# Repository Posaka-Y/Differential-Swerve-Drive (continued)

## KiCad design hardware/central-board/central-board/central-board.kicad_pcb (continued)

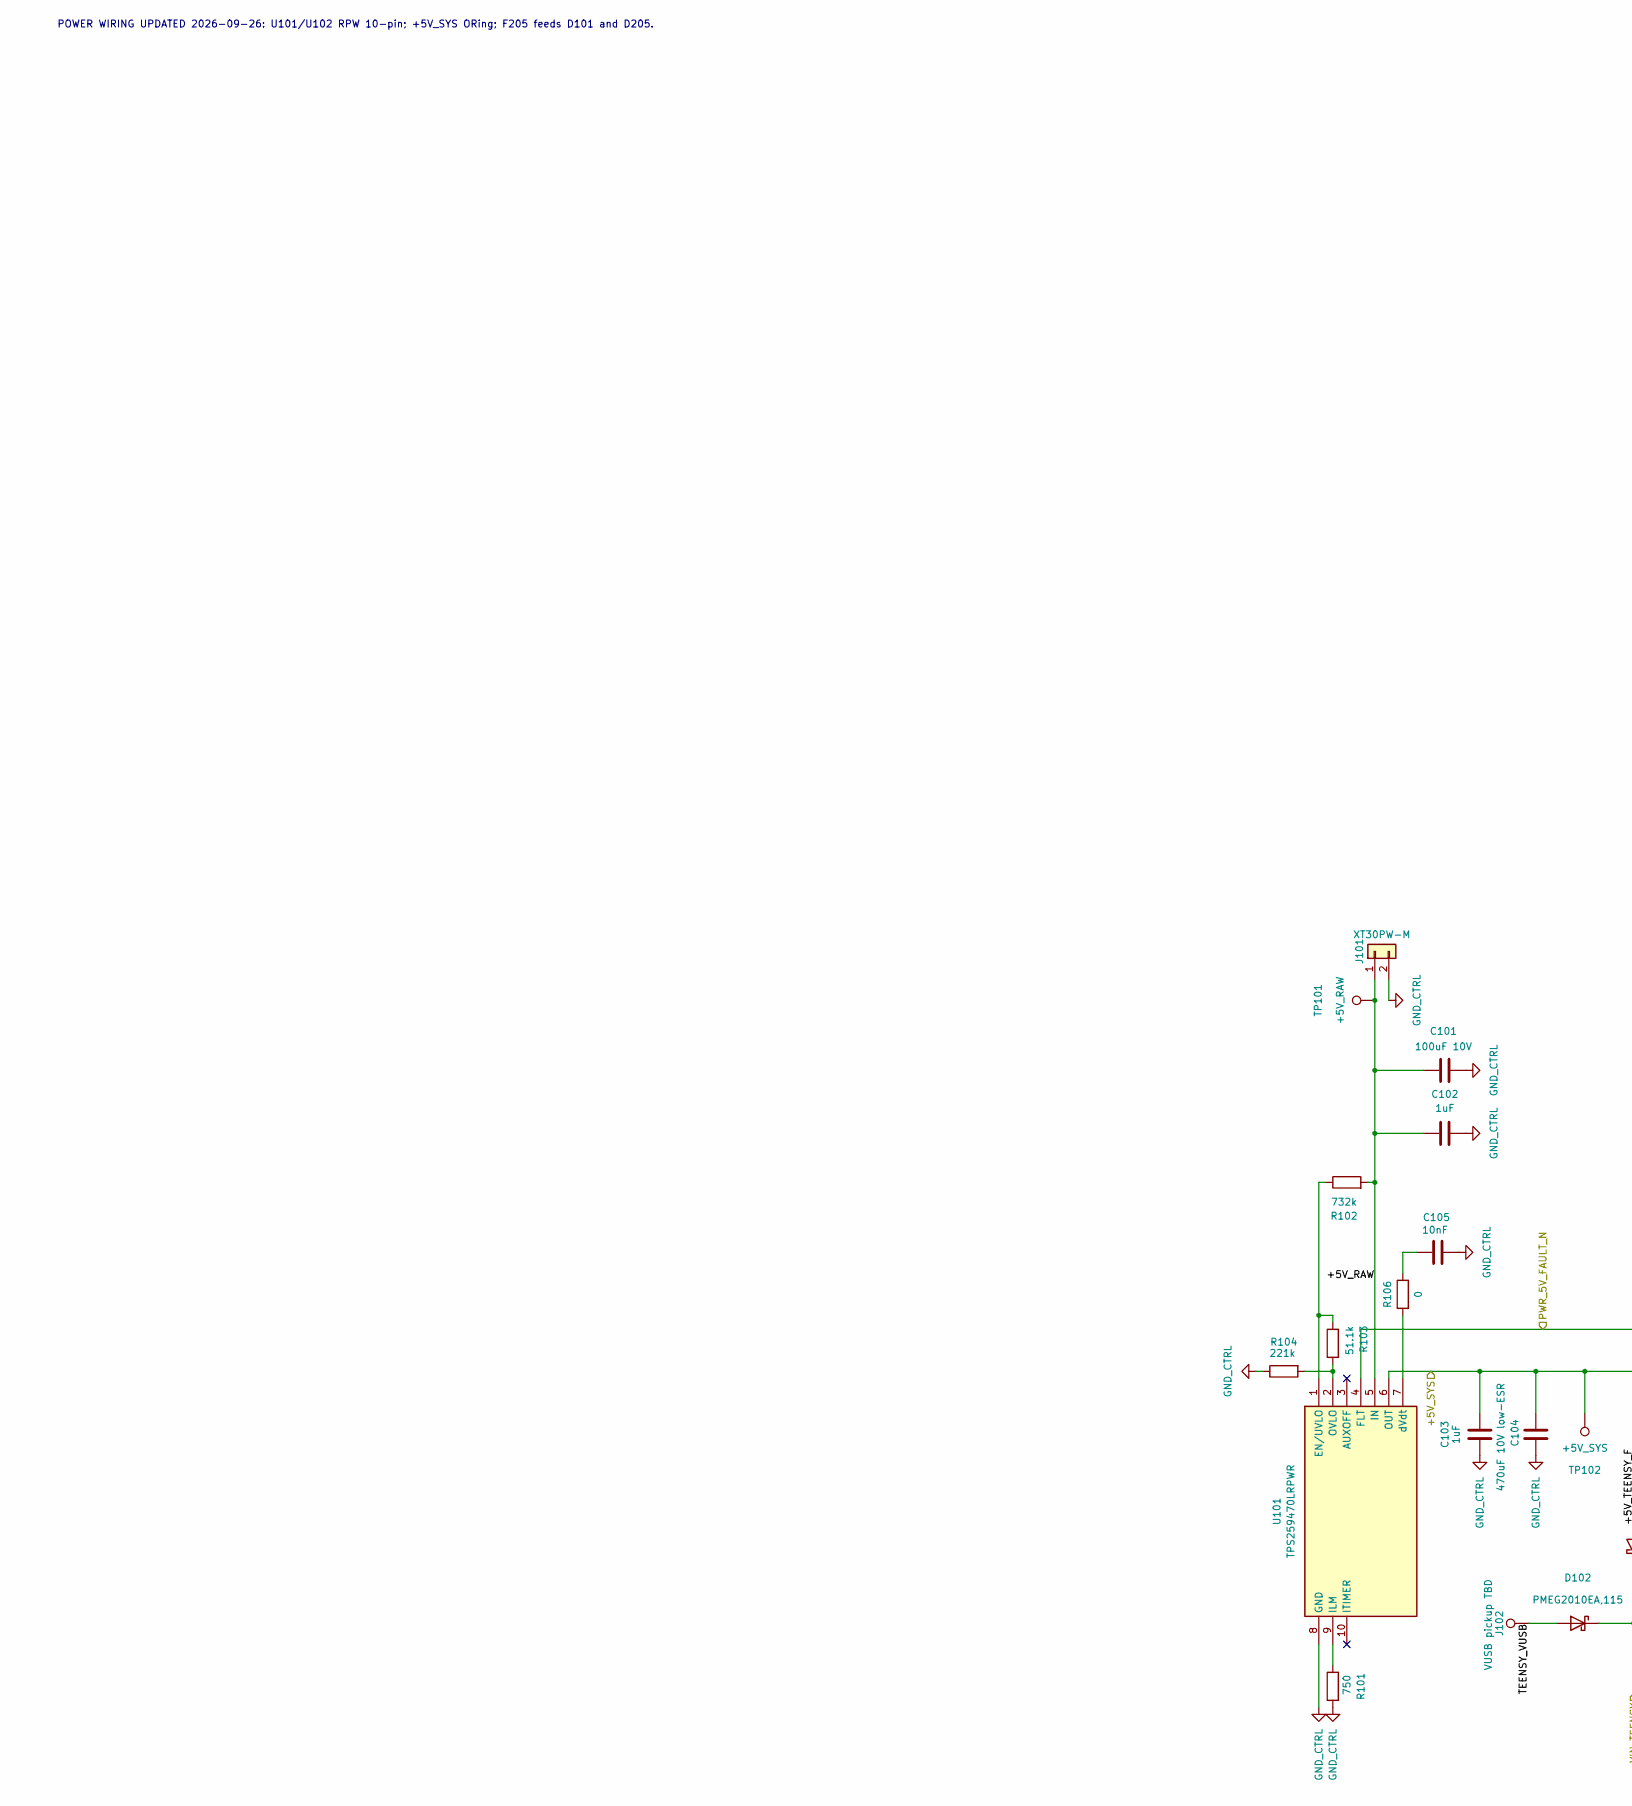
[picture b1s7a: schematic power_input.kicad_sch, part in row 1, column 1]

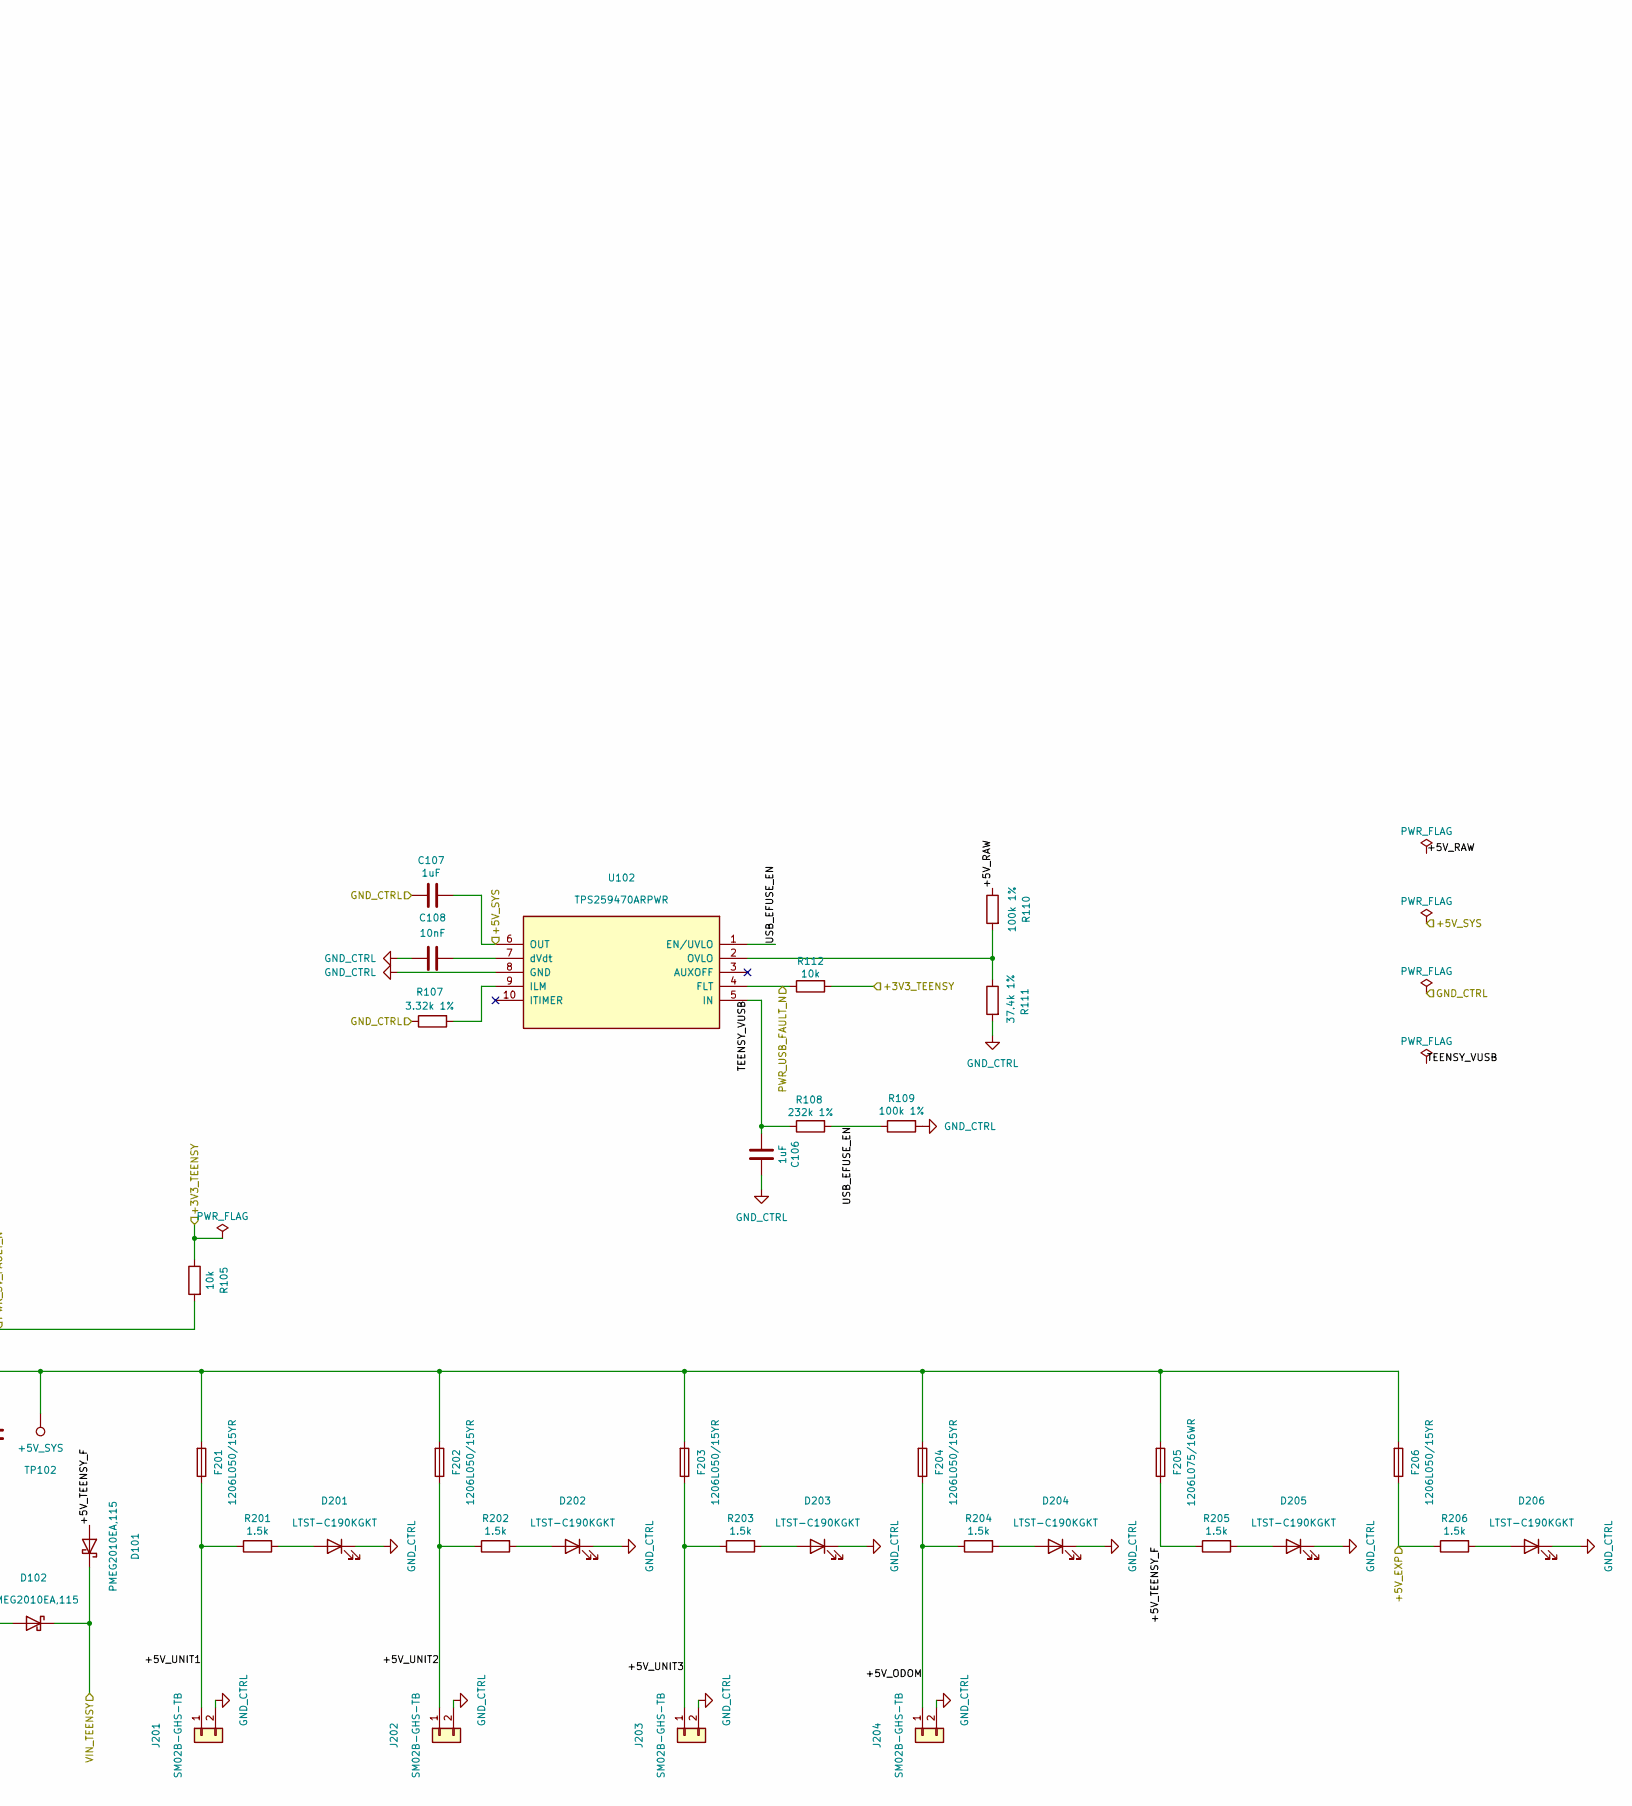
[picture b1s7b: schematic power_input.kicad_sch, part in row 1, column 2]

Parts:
C101: 100uF 10V
C102, C103, C106, C107: 1uF; C_0603_1608Metric
C104: 470uF 10V low-ESR
C105, C108: 10nF; C_0603_1608Metric
D101, D102: PMEG2010EA,115; D_SOD-323
D201, D202, D203, D204, D205, D206: LTST-C190KGKT; LED_0603_1608Metric
F201, F202, F203, F204, F206: 1206L050/15YR; Fuse_1206_3216Metric
F205: 1206L075/16WR; Fuse_1206_3216Metric
J101: XT30PW-M; AMASS_XT30PW-M_1x02_P2.50mm_Horizontal
J102: VUSB pickup TBD
J201, J202, J203, J204: SM02B-GHS-TB; JST_GH_SM02B-GHS-TB_1x02-1MP_P1.25mm_Horizontal
R101: 750; R_0603_1608Metric
R102: 732k; R_0603_1608Metric
R103: 51.1k; R_0603_1608Metric
R104: 221k; R_0603_1608Metric
R105, R112: 10k; R_0603_1608Metric
R106: 0; R_0603_1608Metric
R107: 3.32k 1%; R_0603_1608Metric
R108: 232k 1%; R_0603_1608Metric
R109, R110: 100k 1%; R_0603_1608Metric
R111: 37.4k 1%; R_0603_1608Metric
R201, R202, R203, R204, R205, R206: 1.5k; R_0603_1608Metric
TP101: +5V_RAW; Harwin_S1751-46R
TP102: +5V_SYS; Harwin_S1751-46R
U101: TPS259470LRPWR; TPS25947_RPW_10Pin; Manufacturer_Part_Number TPS259470LRPWR; Mouser Part Number 595-TPS259470LRPWR
U102: TPS259470ARPWR; TPS25947_RPW_10Pin

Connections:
/5V input / eFuse / USB diode OR (1)/+5V_ODOM: F204.1, J204.1, R204.1
/5V input / eFuse / USB diode OR (1)/+5V_RAW: C101.1, C102.1, J101.1, R102.2, R110.1, TP101.1 (1_1), U101.5 (IN)
/5V input / eFuse / USB diode OR (1)/+5V_TEENSY_F: D101.2 (A), F205.1, R205.1
/5V input / eFuse / USB diode OR (1)/+5V_UNIT1: F201.1, J201.1, R201.1
/5V input / eFuse / USB diode OR (1)/+5V_UNIT2: F202.1, J202.1, R202.1
/5V input / eFuse / USB diode OR (1)/+5V_UNIT3: F203.1, J203.1, R203.1
/5V input / eFuse / USB diode OR (1)/TEENSY_VUSB: C106.1, D102.2 (A), J102.1, R108.1, U102.5 (IN)
/5V input / eFuse / USB diode OR (1)/USB_EFUSE_EN: R108.2, R109.1, U102.1 (EN/UVLO)
/+3V3_TEENSY: R105.1, R112.2; also elsewhere on the board
/+5V_EXP: F206.1, R206.1; also elsewhere on the board
/+5V_SYS: C103.2, C104.2, C107.2, F201.2, F202.2, F203.2, F204.2, F205.2, F206.2, TP102.1 (1_1), U101.6 (OUT), U102.6 (OUT); also elsewhere on the board
/PWR_5V_FAULT_N: R105.2, U101.4 (FLT); also elsewhere on the board
/PWR_USB_FAULT_N: R112.1, U102.4 (FLT); also elsewhere on the board
/VIN_TEENSY: D101.1 (K), D102.1 (K); also elsewhere on the board
GND_CTRL: C101.2, C102.2, C103.1, C104.1, C105.2, C106.2, C107.1, C108.1, D201.1 (K), D202.1 (K), D203.1 (K), D204.1 (K), D205.1 (K), D206.1 (K), J101.2, J201.2, J202.2, J203.2, J204.2, R101.2, R104.1, R107.1, R109.2, R111.2, U101.8 (GND), U102.8 (GND); also elsewhere on the board
unnamed: C105.1, R106.1
unnamed: D201.2 (A), R201.2
unnamed: D202.2 (A), R202.2
unnamed: D203.2 (A), R203.2
unnamed: D204.2 (A), R204.2
unnamed: D205.2 (A), R205.2
unnamed: D206.2 (A), R206.2
unnamed: R102.1, R103.1, U101.1 (EN/UVLO)
unnamed: R101.1, U101.9 (ILM)
unnamed: R103.2, R104.2, U101.2 (OVLO)
unnamed: R106.2, U101.7 (dVdt)
unnamed: R107.2, U102.9 (ILM)
unnamed: R110.2, R111.1, U102.2 (OVLO)
unnamed: C108.2, U102.7 (dVdt)

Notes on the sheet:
POWER WIRING UPDATED 2026-09-26: U101/U102 RPW 10-pin; +5V_SYS ORing; F205 feeds D101 and D205.

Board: 2 copper layers, 149 parts (0 on the bottom side), 107 nets, no tracks yet.

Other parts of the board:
H1, H2, H3, H4: MountingHole_3.2mm_M3

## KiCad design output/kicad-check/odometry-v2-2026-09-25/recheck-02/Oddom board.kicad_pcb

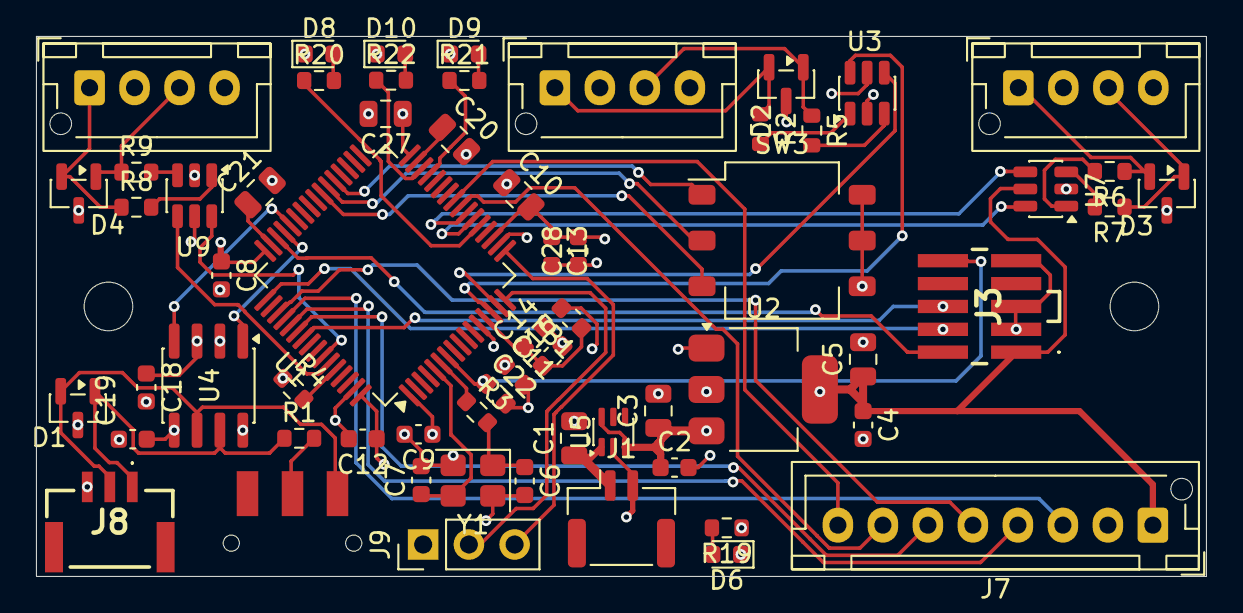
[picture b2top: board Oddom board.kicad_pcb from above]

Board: 4 copper layers, 65.0 x 30.0 mm, 62 parts (0 on the bottom side), 56 nets.

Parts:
C1: 2.2uF; C_0805_2012Metric
C2, C4, C8, C9, C11, C12, C13, C14, C18, C19, C22, C28: 100nF; C_0603_1608Metric
C3, C5: 10uF; C_0805_2012Metric
C6, C7: 10pF; C_0603_1608Metric
C10: 4.7uF; C_0805_2012Metric
C16: 1uF; C_0603_1608Metric
C20, C21, C27: 2.2 µF; C_0805_2012Metric
D1: ESD2CAN24DBZRQ1; SOT-23
D2, D3, D4: D_TVS_Dual_AACESDS452DBZ; SOT-23
D6, D8: LTST-C190KGKT; LED_0603_1608Metric
D9: LTST-C190KSKT; LED_0603_1608Metric
D10: LTST-C190KRKT; LED_0603_1608Metric
FB1: BLM18AG601SN1D; L_0603_1608Metric
J1: SM02B-GHS-TB; JST_GH_SM02B-GHS-TB_1x02-1MP_P1.25mm_Horizontal
J3: FTSH-105-01-L-DV-K-P; FTSH10501LDVKP
J4, J5, J6: Conn_01x04; JST_XH_B4B-XH-AM_1x04_P2.50mm_Vertical
J7: Conn_01x08; JST_XH_B8B-XH-AM_1x08_P2.50mm_Vertical
J8: BM03B-GHS-TBT_LF__SN_; BM03BGHSTBTLFSN
J9: UART_3V3_1x03; PinHeader_1x03_P2.54mm_Vertical
R1: 120R; R_0603_1608Metric
R2, R5, R6, R7, R8, R9: 100R; R_0603_1608Metric
R3: RC0603JR-070RL 0R; R_0603_1608Metric
R4: RC0603FR-0710KL 10k; R_0603_1608Metric
R19, R20, R21, R22: 1k; R_0603_1608Metric
SW1: JS102011SAQN
SW3: DS04-254-1-03BK-SMT; SW_DIP_SPSTx03_Slide_Omron_A6S-310x_W8.9mm_P2.54mm
U1: STM32F405RGTx; LQFP-64_10x10mm_P0.5mm
U2: TLV76133DCYR; SOT-223-3_TabPin2
U3, U7, U9: 74LVC2G17; SOT-23-6
U4: TCAN1051VDRQ1; SOIC-8_3.9x4.9mm_P1.27mm
U5: LM66100DCKR; SOT-363_SC-70-6
Y1: FC3BAEBDI8.0-T1; Crystal_SMD_3225-4Pin_3.2x2.5mm

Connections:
/AMT102_input1/W1_A: U1.22 (PA6), U7.6
/AMT102_input1/W1_B: U1.23 (PA7), U7.4
/AMT102_input2/W1_A: U1.58 (PB6), U9.6
/AMT102_input2/W1_B: U1.59 (PB7), U9.4
/AMT102_input/W1_A: U1.14 (PA0), U3.6
/AMT102_input/W1_B: U1.15 (PA1), U3.4
/BOOT0: R4.2, U1.60 (BOOT0)
/CAN_interface/COMM_RX: U1.44 (PA11), U4.4 (RXD)
/CAN_interface/COMM_TX: U1.45 (PA12), U4.1 (TXD)
COMM: R21.1, U1.29 (PB10)
ERR: R22.1, U1.30 (PB11)
GND: C1.2, C2.2, C3.2, C4.2, C5.2, C6.2, C7.2, C8.2, C9.2, C10.1, C11.2, C12.2, C13.2, C14.2, C16.2, C18.2, C19.2, C20.2, C21.2, C22.2, C27.2, C28.1, D1.3 (GND), D2.3 (common), D3.3 (common), D4.3 (common), D6.1 (K), D8.1 (K), D9.1 (K), D10.1 (K), J1.2, J3.3, J3.5, J3.9, J4.4, J5.4, J6.4, J7.2, J8.3, J9.1, R4.1, SW3.4, SW3.5, SW3.6, U1.12 (VSSA), U1.18 (VSS), U1.63 (VSS), U2.1 (GND), U3.2 (GND), U4.2 (GND), U4.8 (S), U5.2 (GND), U7.2 (GND), U9.2 (GND), Y1.2 (G), Y1.4 (G)
IMU_CS_N: J7.6, U1.54 (PD2)
IMU_INT1: J7.7, U1.24 (PC4)
IMU_INT2: J7.8, U1.25 (PC5)
NRST: C22.1, J3.10, U1.7 (NRST)
unnamed: C6.1, R3.2, Y1.1
unnamed: D1.1 (IO_1), J8.1, R1.1, U4.7 (CANH)
unnamed: D1.2 (IO_2), J8.2, SW1.3 (N.O.), U4.6 (CANL)
unnamed: D2.1 (A1), J4.3, R5.1
unnamed: D2.2 (A2), J4.1, R2.1
unnamed: D3.1 (A1), J5.3, R7.1
unnamed: D3.2 (A2), J5.1, R6.1
unnamed: D4.1 (A1), J6.3, R9.1
unnamed: D4.2 (A2), J6.1, R8.1
unnamed: D6.2 (A), R19.2
unnamed: D8.2 (A), R20.2
unnamed: D9.2 (A), R21.2
unnamed: D10.2 (A), R22.2
unnamed: C1.1, J1.1, U5.1 (VIN)
unnamed: J7.3, U1.52 (PC11)
unnamed: J7.4, U1.53 (PC12)
unnamed: J7.5, U1.51 (PC10)
unnamed: R2.2, U3.1
unnamed: R5.2, U3.3
unnamed: R6.2, U7.1
unnamed: R7.2, U7.3
unnamed: R8.2, U9.1
unnamed: R9.2, U9.3
unnamed: R1.2, SW1.2 (COM)
unnamed: SW3.1, U1.37 (PC6)
unnamed: SW3.2, U1.38 (PC7)
unnamed: SW3.3, U1.39 (PC8)
unnamed: C7.1, U1.5 (PH0), Y1.3
unnamed: R3.1, U1.6 (PH1)
unnamed: C20.1, U1.31 (VCAP_1)
unnamed: C21.1, U1.47 (VCAP_2)
unnamed: C14.1, C16.1, FB1.1, U1.13 (VDDA)
PWR_3.3V: C4.1, C5.1, C8.1, C9.1, C10.2, C11.1, C12.1, C13.1, C19.1, C27.1, C28.2, FB1.2, J3.1, J7.1, R19.1, U1.1 (VBAT), U1.19 (VDD), U1.32 (VDD), U1.48 (VDD), U1.64 (VDD), U2.2 (VO), U3.5 (VCC), U4.5 (VIO), U7.5 (VCC), U9.5 (VCC)
PWR_5V: C2.1, C3.1, C18.1, J4.2, J5.2, J6.2, U2.3 (VI), U4.3 (VCC), U5.3 (~CE), U5.6 (VOUT)
RUN: R20.1, U1.21 (PA5)
SWCLK: J3.4, U1.49 (PA14)
SWDIO: J3.2, U1.46 (PA13)
SWO: J3.6, U1.55 (PB3)
USART2_RX: J9.3, U1.17 (PA3)
USART2_TX: J9.2, U1.16 (PA2)

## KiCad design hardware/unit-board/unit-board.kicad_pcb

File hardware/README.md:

# hardware

KiCadによる基板設計。共通ブロック方針は `docs/electrical/CARRIER_BOARD_BUILD_PLAN.md` 冒頭を参照。

## 構成

```text
hardware/
  lib/             共通シンボル・フットプリントライブラリ
  blocks/          共通階層シート(can_interface, power_input_5v, status_led, mcu_min_g474)
  unit-board/      差動ステアユニット基板(STM32G474RET6)
  central-board/   中央制御ボード(Teensy 4.1)
  odometry-board/  オドメトリ基板(STM32F405RGT6 + AMT102 A/B相 x3)
  reference/       流用元プロジェクト(下表)
```

## 流用元(reference/)

| 参照 | 形式 | 流用するブロック | ライセンス |
|---|---|---|---|
| `candleLightFD/` ([linux-automation/candleLightFD](https://github.com/linux-automation/candleLightFD)) | **KiCadソース**(階層シート: MCU / PSU / transceiver) | CANトランシーバ周り(TJA1051T/3 + 100nF + 120Ω)→ `TCAN1051VDRQ1`に置換して `blocks/can_interface` の下敷きにする。階層シートの切り方・リリースフォルダ構成(製造データの出し方)も運用の手本になる | CERN-OHL v1.2(流用時はライセンス表記を維持) |
| `mks-canable-v2.0-schematic.pdf` ([makerbase-mks/CANable-MKS](https://github.com/makerbase-mks/CANable-MKS)) | PDF回路図 | STM32G431のMCU最小構成(電源、BOOT0、水晶、SWD)。G474RET6版を起こすときの照合用 | 回路図公開(リポジトリ記載に従う) |
| `nucleo-g474re-mb1367-c05-schematic.pdf`(ST MB1367)**※未取得** | PDF回路図 | **G474RET6そのものの最小構成の正解例**(VDD/VDDA処理、NRST、BOOT0、HSE周り)。ピンごとのデカップリング数の確認はこれを正とする | ST評価ボード回路図(参照用) |
| `ARK_CANNODE/` ([ARK-Electronics/ARK_CANNODE](https://github.com/ARK-Electronics/ARK_CANNODE)) | PDF回路図 + BOM(`Hardware/Rev 1/`) | 逆接保護(LM66100)、CANコネクタ2個並列のデイジーチェーン渡り、外部信号のESDダイオード、TJA1051+FET切替終端(参考のみ)。詳細は`CARRIER_BOARD_REQUIREMENTS.md`「回路図作成メモ」 | リポジトリのLICENSE参照 |
| `datasheets/` | データシートPDF | AMT22 rev1.10(コネクタピン順1=+5V/2=SCLK/3=MOSI/4=GND/5=MISO/6=CS)、PESD1CAN rev04(1/2=ライン、3=GND) | メーカー資料(参照用) |

※ MB1367回路図はst.comが自動取得を弾くため手動ダウンロードが必要:
<https://www.st.com/resource/en/schematic_pack/mb1367-g474re-c05_schematic.pdf>(または c04)。取得したらこのフォルダに上記ファイル名で保存する。

## 設計ルール

- 回路図のネット名は `docs/communication/COMMUNICATION_NAMING_AND_IDS.md` の命名に従う(`COMM_A/B`、`C620_CAN_*`、`PWR_*`、`_N`)。
- ピン割当は `docs/electrical/CARRIER_BOARD_REQUIREMENTS.md`(ユニット)/ `ODOMETRY_BOARD_REQUIREMENTS.md`(オドメトリ)の表が正本。
- シンボル・フットプリントは`lib/`に置き、KiCad標準ライブラリ依存を減らす(後続プロジェクトへの持ち出しやすさ優先)。
- プロジェクト固有ライブラリの収録範囲と標準ライブラリ割当は`lib/LIBRARY_MANIFEST.md`を正本とする。標準部品を無理由に複製しない。
- 発注前チェックは `docs/checklists/REVIEW_CHECKLIST.md`。

## CLI検証

KiCad 10で保存した回路図・PCBは、リポジトリルートから次で検証する。

```powershell
.\tools\kicad\check.ps1
```

既定では `hardware/unit-board/unit-board` を対象にERC、回路図PDF出力、DRCを実行し、結果を
`$env:TEMP\differential-swerve-kicad-check` へ保存する。CI相当の厳格な確認では
`-FailOnViolations`を付け、ERC/DRC違反があれば終了コードを非0にする。

PCB未着手の段階で回路図だけを厳格確認する場合は、空PCBのDRCを省く。

```powershell
.\tools\kicad\check.ps1 -FailOnViolations -SkipDrc
```

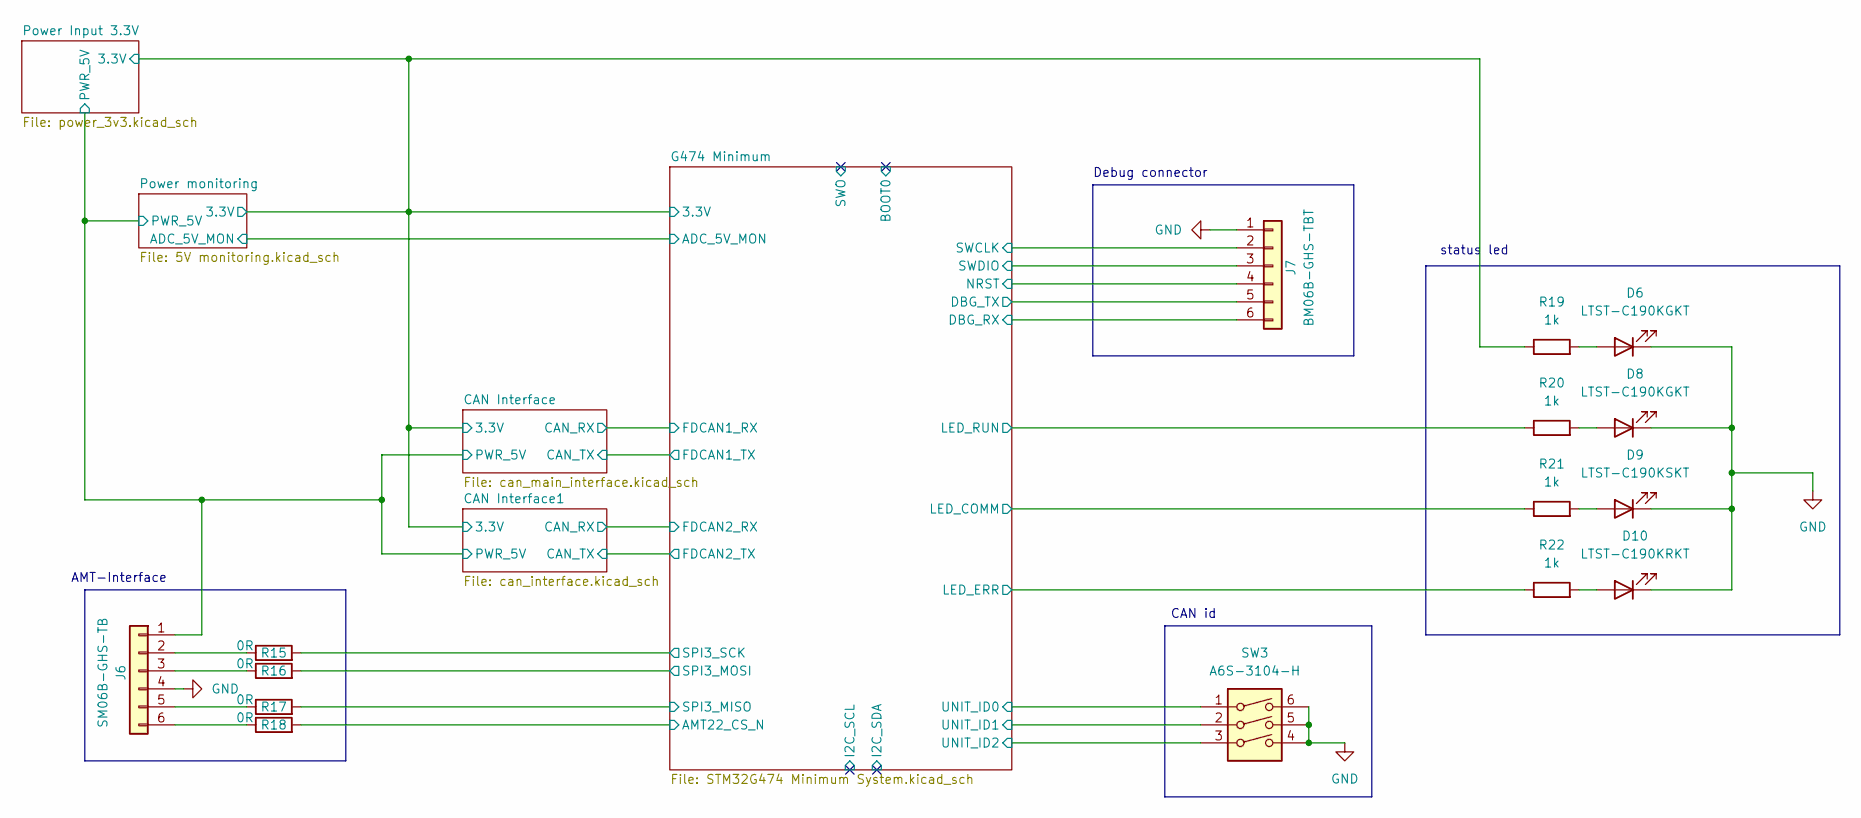
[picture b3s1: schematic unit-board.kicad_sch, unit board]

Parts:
D6, D8: LTST-C190KGKT; LED_0603_1608Metric
D9: LTST-C190KSKT; LED_0603_1608Metric
D10: LTST-C190KRKT; LED_0603_1608Metric
J6: SM06B-GHS-TB; JST_GH_SM06B-GHS-TB_1x06-1MP_P1.25mm_Horizontal
J7: BM06B-GHS-TBT; JST_GH_BM06B-GHS-TBT_1x06-1MP_P1.25mm_Vertical
R15, R16, R17, R18: 0R; R_0603_1608Metric
R19, R20, R21, R22: 1k; R_0603_1608Metric
SW3: A6S-3104-H; SW_DIP_SPSTx03_Slide_Omron_A6S-310x_W8.9mm_P2.54mm

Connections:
/CAN Interface/3.3V: R19.1; also elsewhere on the board
/CAN Interface/PWR_5V: J6.1; also elsewhere on the board
/G474 Minimum/AMT22_CS_N: R18.2; also elsewhere on the board
/G474 Minimum/DBG_RX: J7.6; also elsewhere on the board
/G474 Minimum/DBG_TX: J7.5; also elsewhere on the board
/G474 Minimum/LED_COMM: R21.1; also elsewhere on the board
/G474 Minimum/LED_ERR: R22.1; also elsewhere on the board
/G474 Minimum/LED_RUN: R20.1; also elsewhere on the board
/G474 Minimum/NRST: J7.4; also elsewhere on the board
/G474 Minimum/SPI3_MISO: R17.2; also elsewhere on the board
/G474 Minimum/SPI3_MOSI: R16.2; also elsewhere on the board
/G474 Minimum/SPI3_SCK: R15.2; also elsewhere on the board
/G474 Minimum/SWCLK: J7.2; also elsewhere on the board
/G474 Minimum/SWDIO: J7.3; also elsewhere on the board
/G474 Minimum/UNIT_ID0: SW3.1; also elsewhere on the board
/G474 Minimum/UNIT_ID1: SW3.2; also elsewhere on the board
/G474 Minimum/UNIT_ID2: SW3.3; also elsewhere on the board
GND: D6.1 (K), D8.1 (K), D9.1 (K), D10.1 (K), J6.4, J7.1, SW3.4, SW3.5, SW3.6; also elsewhere on the board
unnamed: D6.2 (A), R19.2
unnamed: D8.2 (A), R20.2
unnamed: D9.2 (A), R21.2
unnamed: D10.2 (A), R22.2
unnamed: J6.2, R15.1
unnamed: J6.3, R16.1
unnamed: J6.5, R17.1
unnamed: J6.6, R18.1

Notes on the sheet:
Debug connector
AMT-Interface
status led
CAN id

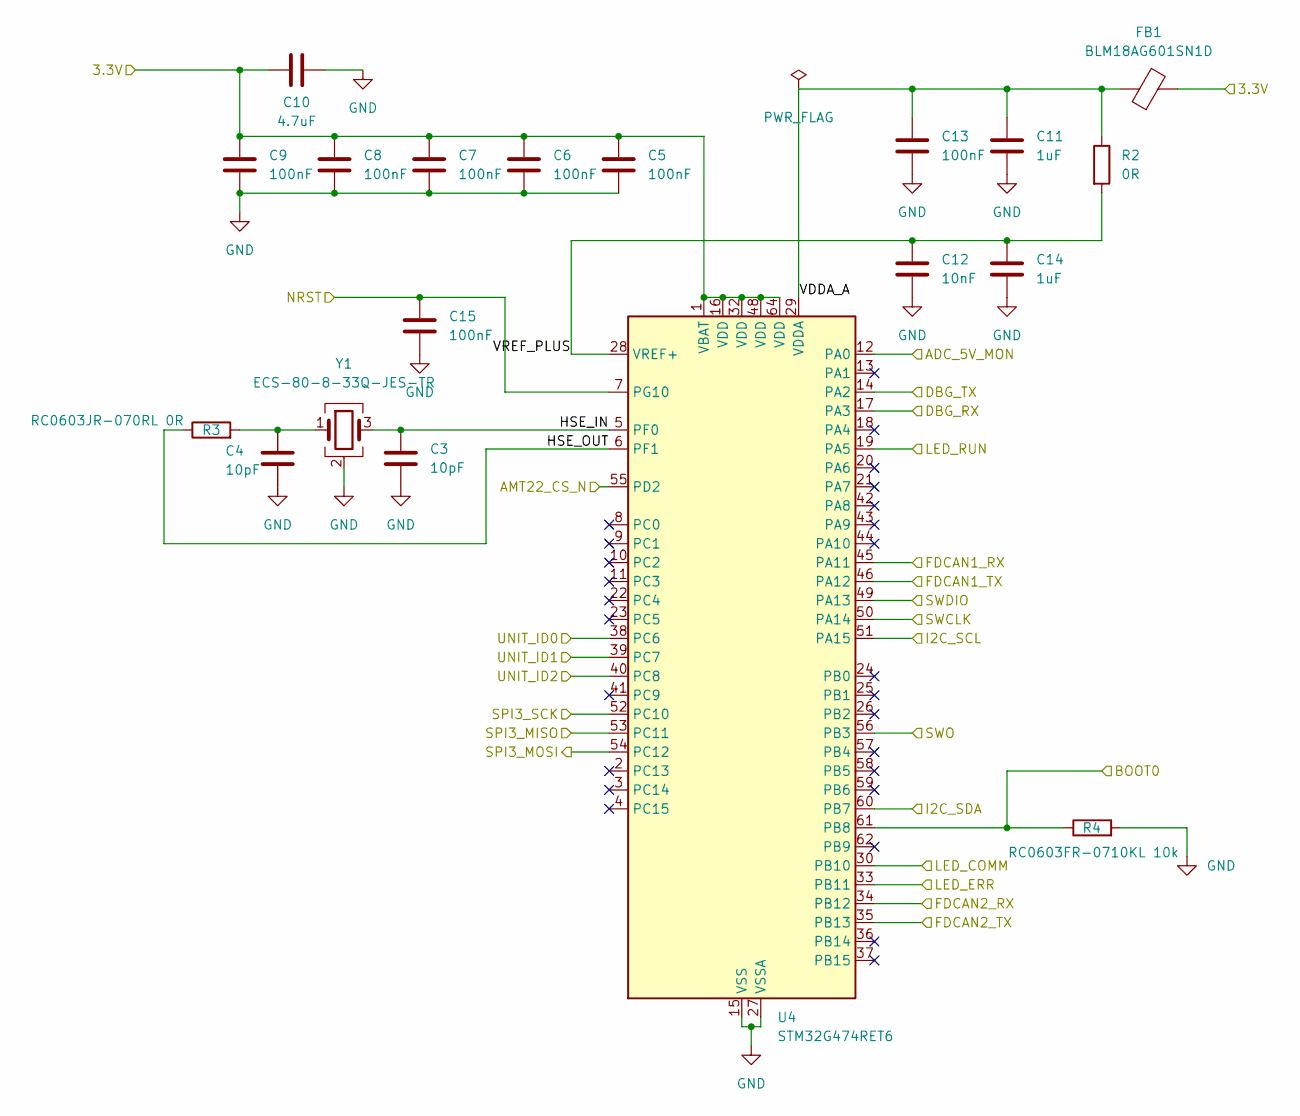
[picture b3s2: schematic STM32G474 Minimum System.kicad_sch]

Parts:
C3, C4: 10pF; C_0603_1608Metric
C5, C6, C7, C8, C9, C13, C15: 100nF; C_0603_1608Metric
C10: 4.7uF; C_0805_2012Metric
C11, C14: 1uF; C_0603_1608Metric
C12: 10nF; C_0603_1608Metric
FB1: BLM18AG601SN1D; L_0603_1608Metric
R2: 0R; R_0603_1608Metric
R3: RC0603JR-070RL 0R; R_0603_1608Metric
R4: RC0603FR-0710KL 10k; R_0603_1608Metric
U4: STM32G474RET6; LQFP-64_10x10mm_P0.5mm
Y1: ECS-80-8-33Q-JES-TR; Crystal_SMD_3225-4Pin_3.2x2.5mm

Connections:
/CAN Interface1/CAN_RX: U4.34 (PB12); also elsewhere on the board
/CAN Interface1/CAN_TX: U4.35 (PB13); also elsewhere on the board
/CAN Interface/3.3V: C5.1, C6.1, C7.1, C8.1, C9.1, C10.2, FB1.2, U4.1 (VBAT), U4.16 (VDD), U4.32 (VDD), U4.48 (VDD), U4.64 (VDD); also elsewhere on the board
/CAN Interface/CAN_RX: U4.45 (PA11); also elsewhere on the board
/CAN Interface/CAN_TX: U4.46 (PA12); also elsewhere on the board
/G474 Minimum/ADC_5V_MON: U4.12 (PA0); also elsewhere on the board
/G474 Minimum/AMT22_CS_N: U4.55 (PD2); also elsewhere on the board
/G474 Minimum/BOOT0: R4.1, U4.61 (PB8)
/G474 Minimum/DBG_RX: U4.17 (PA3); also elsewhere on the board
/G474 Minimum/DBG_TX: U4.14 (PA2); also elsewhere on the board
/G474 Minimum/HSE_IN: C3.1, U4.5 (PF0), Y1.3
/G474 Minimum/HSE_OUT: R3.1, U4.6 (PF1)
/G474 Minimum/I2C_SCL: U4.51 (PA15)
/G474 Minimum/I2C_SDA: U4.60 (PB7)
/G474 Minimum/LED_COMM: U4.30 (PB10); also elsewhere on the board
/G474 Minimum/LED_ERR: U4.33 (PB11); also elsewhere on the board
/G474 Minimum/LED_RUN: U4.19 (PA5); also elsewhere on the board
/G474 Minimum/NRST: C15.1, U4.7 (PG10); also elsewhere on the board
/G474 Minimum/SPI3_MISO: U4.53 (PC11); also elsewhere on the board
/G474 Minimum/SPI3_MOSI: U4.54 (PC12); also elsewhere on the board
/G474 Minimum/SPI3_SCK: U4.52 (PC10); also elsewhere on the board
/G474 Minimum/SWCLK: U4.50 (PA14); also elsewhere on the board
/G474 Minimum/SWDIO: U4.49 (PA13); also elsewhere on the board
/G474 Minimum/SWO: U4.56 (PB3)
/G474 Minimum/UNIT_ID0: U4.38 (PC6); also elsewhere on the board
/G474 Minimum/UNIT_ID1: U4.39 (PC7); also elsewhere on the board
/G474 Minimum/UNIT_ID2: U4.40 (PC8); also elsewhere on the board
/G474 Minimum/VDDA_A: C11.1, C13.1, FB1.1, R2.1, U4.29 (VDDA)
/G474 Minimum/VREF_PLUS: C12.1, C14.1, R2.2, U4.28 (VREF+)
GND: C3.2, C4.2, C5.2, C6.2, C7.2, C8.2, C9.2, C10.1, C11.2, C12.2, C13.2, C14.2, C15.2, R4.2, U4.15 (VSS), U4.27 (VSSA), U4.31 (VSS), U4.47 (VSS), U4.63 (VSS), Y1.2 (G), Y1.4 (G); also elsewhere on the board
unnamed: C4.1, R3.2, Y1.1

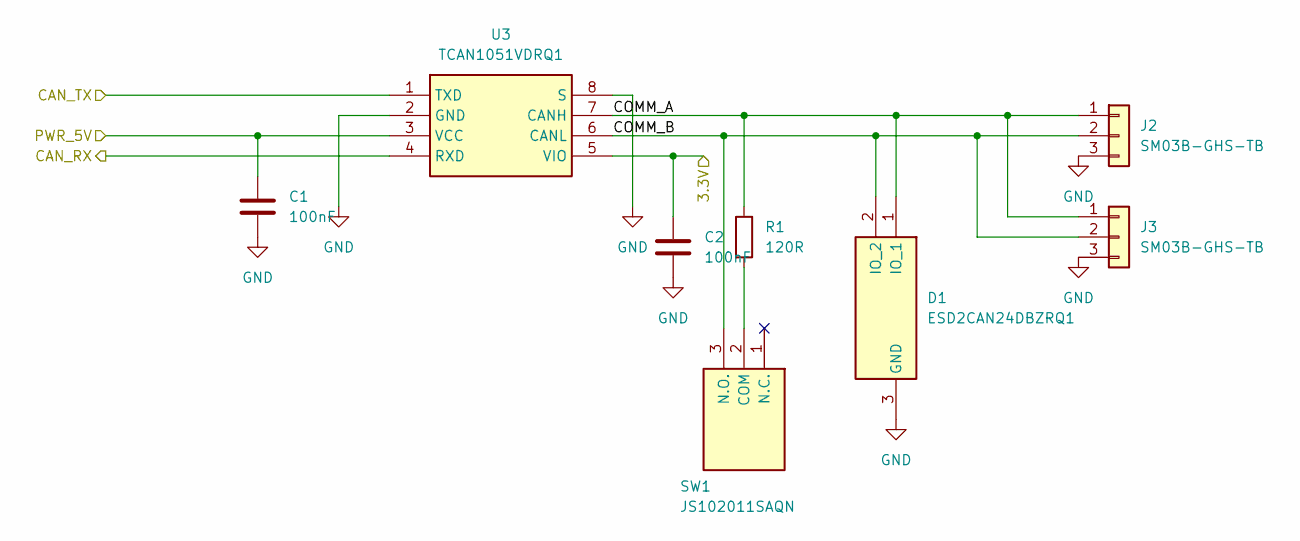
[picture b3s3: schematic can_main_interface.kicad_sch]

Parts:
C1, C2: 100nF; C_0603_1608Metric
D1: ESD2CAN24DBZRQ1; SOT-23; Manufacturer_Part_Number ESD2CAN24DBZRQ1; Mouser Part Number 595-ESD2CAN24DBZRQ1
J2, J3: SM03B-GHS-TB; JST_GH_SM03B-GHS-TB_1x03-1MP_P1.25mm_Horizontal
R1: 120R; R_0603_1608Metric
SW1: JS102011SAQN; Manufacturer_Part_Number JS102011SAQN; Mouser Part Number 611-JS102011SAQN
U3: TCAN1051VDRQ1; SOIC-8_3.9x4.9mm_P1.27mm; Manufacturer_Part_Number TCAN1051VDRQ1; Mouser Part Number 595-TCAN1051VDRQ1

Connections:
/CAN Interface/3.3V: C2.1, U3.5 (VIO); also elsewhere on the board
/CAN Interface/CAN_RX: U3.4 (RXD); also elsewhere on the board
/CAN Interface/CAN_TX: U3.1 (TXD); also elsewhere on the board
/CAN Interface/COMM_A: D1.1 (IO_1), J2.1, J3.1, R1.1, U3.7 (CANH)
/CAN Interface/COMM_B: D1.2 (IO_2), J2.2, J3.2, SW1.3 (N.O.), U3.6 (CANL)
/CAN Interface/PWR_5V: C1.1, U3.3 (VCC); also elsewhere on the board
GND: C1.2, C2.2, D1.3 (GND), J2.3, J3.3, U3.2 (GND), U3.8 (S); also elsewhere on the board
unnamed: R1.2, SW1.2 (COM)

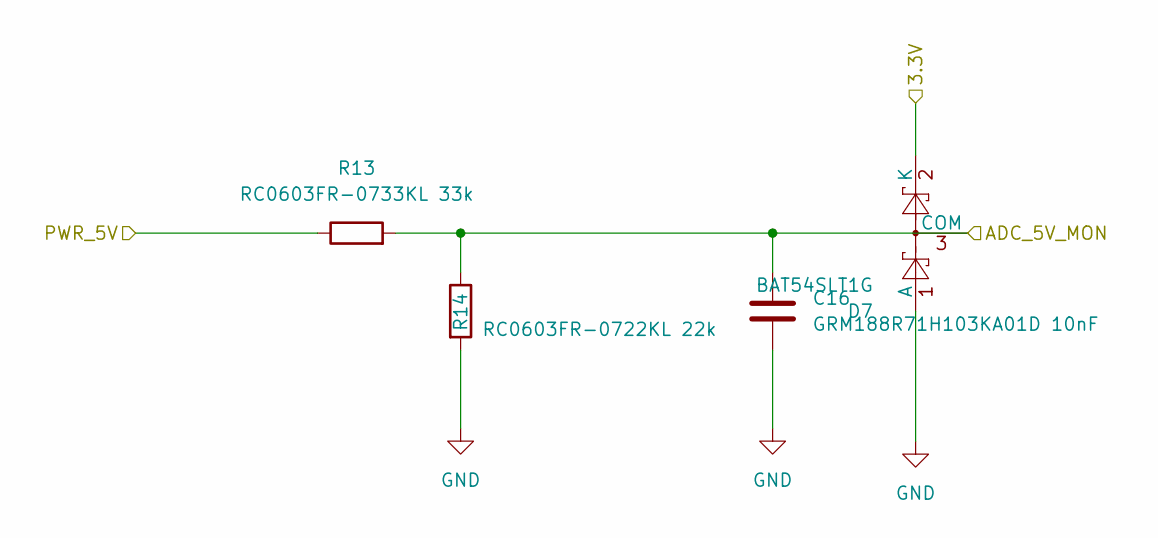
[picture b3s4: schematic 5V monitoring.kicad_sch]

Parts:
C16: GRM188R71H103KA01D 10nF; C_0603_1608Metric
D7: BAT54SLT1G; SOT-23
R13: RC0603FR-0733KL 33k; R_0603_1608Metric
R14: RC0603FR-0722KL 22k; R_0603_1608Metric

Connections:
/CAN Interface/3.3V: D7.2 (K); also elsewhere on the board
/CAN Interface/PWR_5V: R13.1; also elsewhere on the board
/G474 Minimum/ADC_5V_MON: C16.1, D7.3 (COM), R13.2, R14.1; also elsewhere on the board
GND: C16.2, D7.1 (A), R14.2; also elsewhere on the board

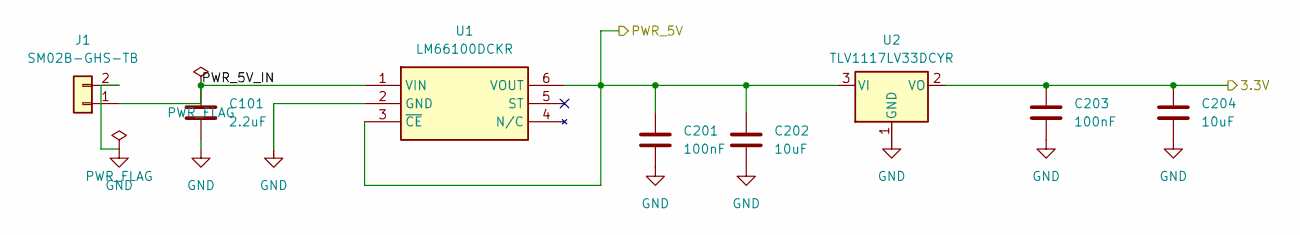
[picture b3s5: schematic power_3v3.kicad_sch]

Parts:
C101: 2.2uF; C_0805_2012Metric
C201, C203: 100nF; C_0603_1608Metric
C202, C204: 10uF; C_0805_2012Metric
J1: SM02B-GHS-TB; JST_GH_SM02B-GHS-TB_1x02-1MP_P1.25mm_Horizontal
U1: LM66100DCKR; SOT-363_SC-70-6; Manufacturer_Part_Number LM66100DCKR; Mouser Part Number 595-LM66100DCKR
U2: TLV1117LV33DCYR; SOT-223-3_TabPin2

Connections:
/CAN Interface/3.3V: C203.1, C204.1, U2.2 (VO); also elsewhere on the board
/CAN Interface/PWR_5V: C201.1, C202.1, U1.3 (~CE), U1.6 (VOUT), U2.3 (VI); also elsewhere on the board
/Power Input 3.3V/PWR_5V_IN: C101.1, J1.1, U1.1 (VIN)
GND: C101.2, C201.2, C202.2, C203.2, C204.2, J1.2, U1.2 (GND), U2.1 (GND); also elsewhere on the board

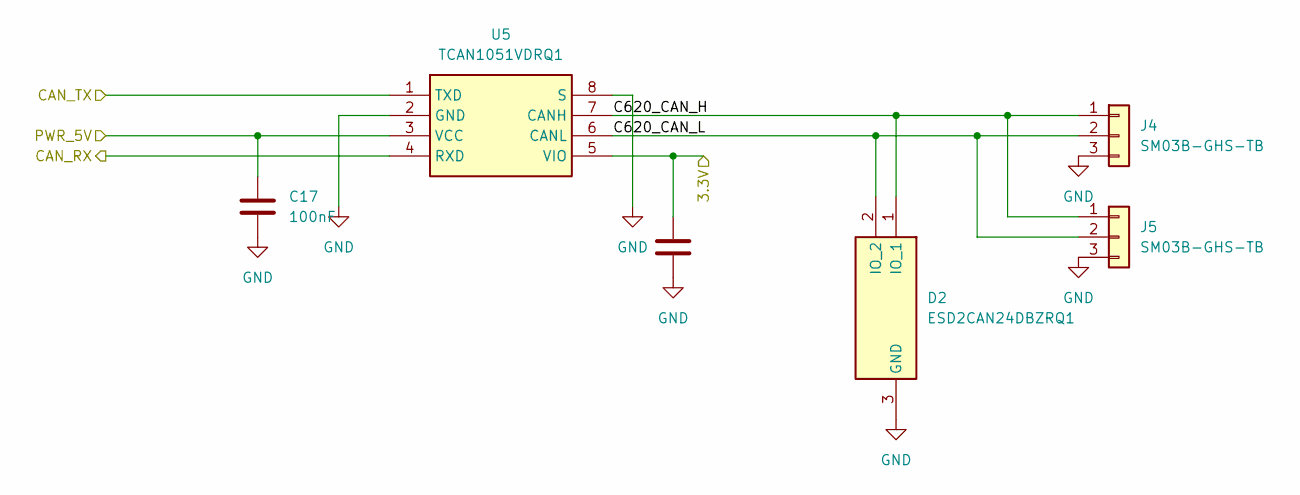
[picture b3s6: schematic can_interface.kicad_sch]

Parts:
C17, C18: 100nF; C_0603_1608Metric
D2: ESD2CAN24DBZRQ1; SOT-23; Manufacturer_Part_Number ESD2CAN24DBZRQ1; Mouser Part Number 595-ESD2CAN24DBZRQ1
J4, J5: SM03B-GHS-TB; JST_GH_SM03B-GHS-TB_1x03-1MP_P1.25mm_Horizontal
U5: TCAN1051VDRQ1; SOIC-8_3.9x4.9mm_P1.27mm; Manufacturer_Part_Number TCAN1051VDRQ1; Mouser Part Number 595-TCAN1051VDRQ1

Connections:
/CAN Interface1/C620_CAN_H: D2.1 (IO_1), J4.1, J5.1, U5.7 (CANH)
/CAN Interface1/C620_CAN_L: D2.2 (IO_2), J4.2, J5.2, U5.6 (CANL)
/CAN Interface1/CAN_RX: U5.4 (RXD); also elsewhere on the board
/CAN Interface1/CAN_TX: U5.1 (TXD); also elsewhere on the board
/CAN Interface/3.3V: C18.1, U5.5 (VIO); also elsewhere on the board
/CAN Interface/PWR_5V: C17.1, U5.3 (VCC); also elsewhere on the board
GND: C17.2, C18.2, D2.3 (GND), J4.3, J5.3, U5.2 (GND), U5.8 (S); also elsewhere on the board

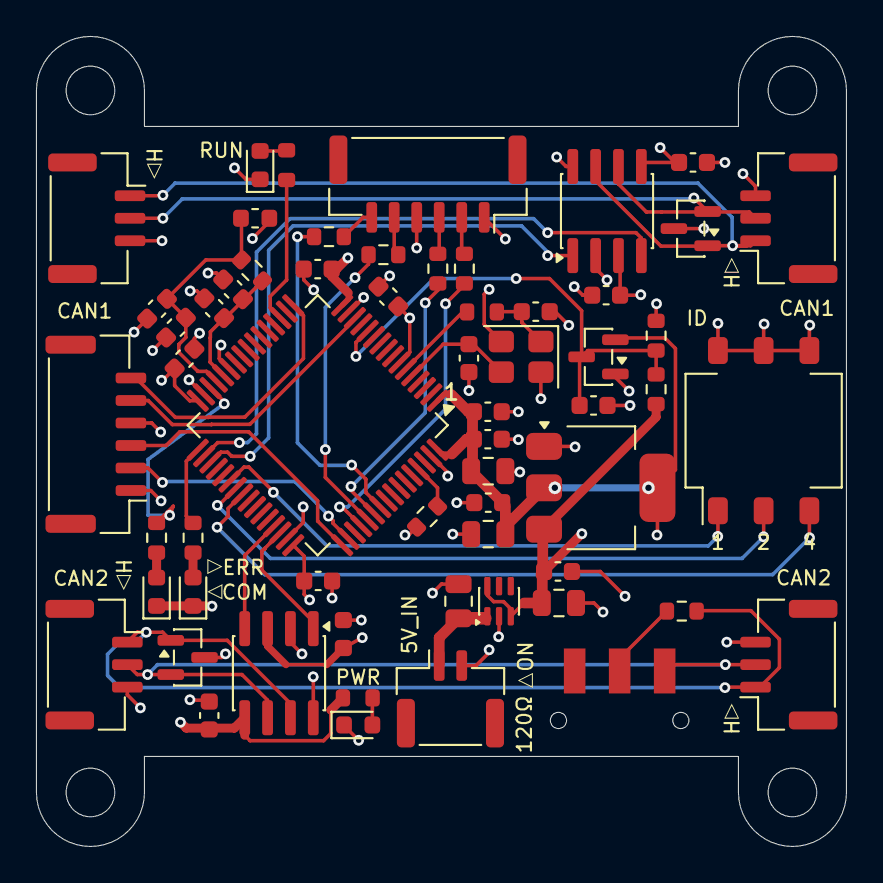
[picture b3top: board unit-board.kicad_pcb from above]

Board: 4 copper layers, 45.0 x 45.0 mm, 61 parts (0 on the bottom side), 43 nets.

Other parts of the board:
QR*****: QR_GitHub_Repository
